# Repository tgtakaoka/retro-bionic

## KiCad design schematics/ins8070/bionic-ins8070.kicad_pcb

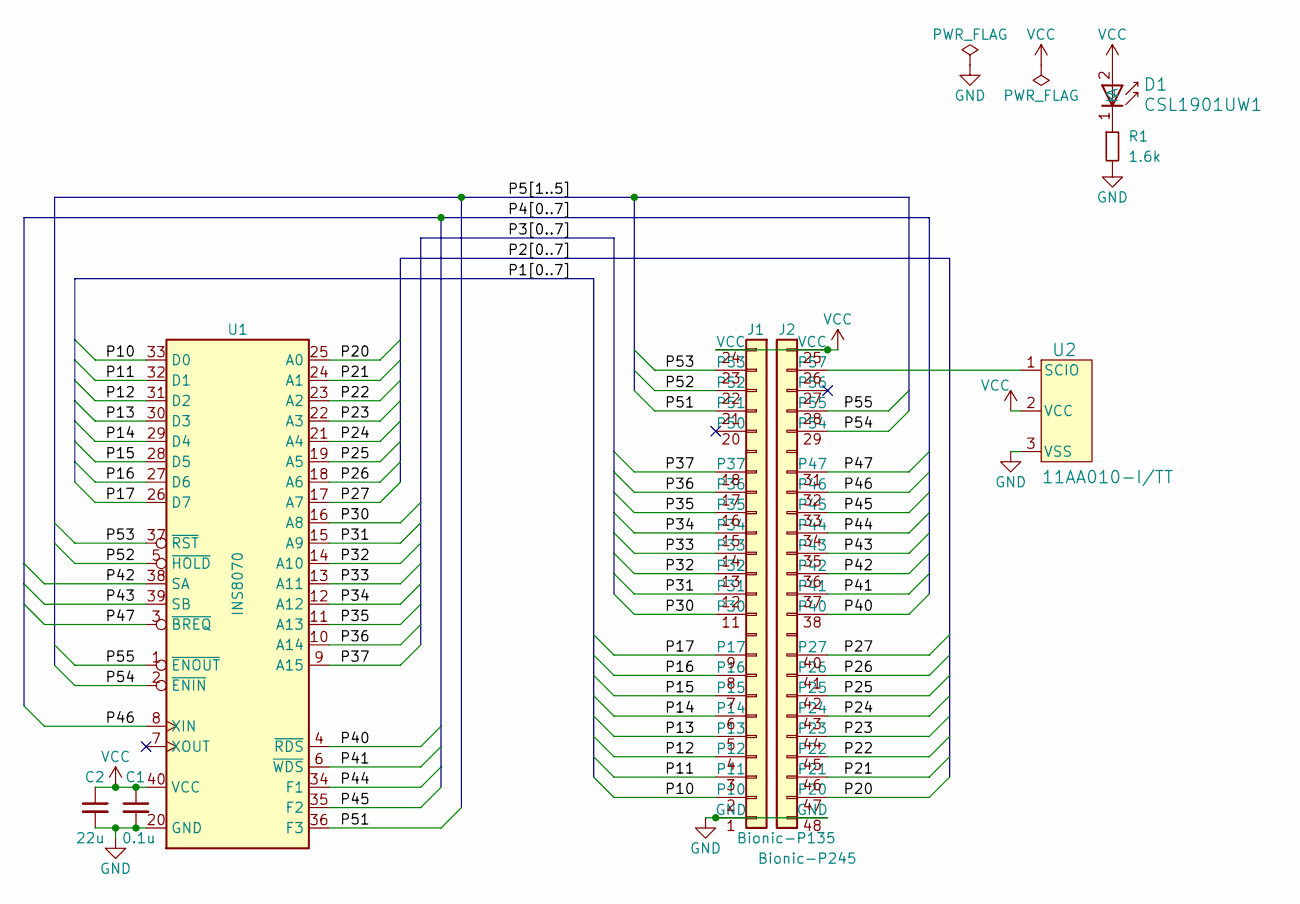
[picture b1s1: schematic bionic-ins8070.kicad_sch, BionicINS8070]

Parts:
C1: 0.1u; C_0603_1608Metric_Pad1.08x0.95mm_HandSolder
C2: 22u; C_0603_1608Metric_Pad1.08x0.95mm_HandSolder
D1: CSL1901UW1; LED_CSL1901UW1_ROM-M
J1: Bionic-P135; Bionic-P135_THT
J2: Bionic-P245; Bionic-P245_THT
R1: 1.6k; R_0603_1608Metric_Pad0.98x0.95mm_HandSolder
U1: INS8070; DIP-40_W15.24mm_Socket
U2: 11AA010-I/TT; SOT-23_MC_MCH-M

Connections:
/P10: J1.2 (P10), U1.33 (D0)
/P11: J1.3 (P11), U1.32 (D1)
/P12: J1.4 (P12), U1.31 (D2)
/P13: J1.5 (P13), U1.30 (D3)
/P14: J1.6 (P14), U1.29 (D4)
/P15: J1.7 (P15), U1.28 (D5)
/P16: J1.8 (P16), U1.27 (D6)
/P17: J1.9 (P17), U1.26 (D7)
/P20: J2.47 (P20), U1.25 (A0)
/P21: J2.46 (P21), U1.24 (A1)
/P22: J2.45 (P22), U1.23 (A2)
/P23: J2.44 (P23), U1.22 (A3)
/P24: J2.43 (P24), U1.21 (A4)
/P25: J2.42 (P25), U1.19 (A5)
/P26: J2.41 (P26), U1.18 (A6)
/P27: J2.40 (P27), U1.17 (A7)
/P30: J1.11 (P30), U1.16 (A8)
/P31: J1.12 (P31), U1.15 (A9)
/P32: J1.13 (P32), U1.14 (A10)
/P33: J1.14 (P33), U1.13 (A11)
/P34: J1.15 (P34), U1.12 (A12)
/P35: J1.16 (P35), U1.11 (A13)
/P36: J1.17 (P36), U1.10 (A14)
/P37: J1.18 (P37), U1.9 (A15)
/P40: J2.38 (P40), U1.4 (~RDS)
/P41: J2.37 (P41), U1.6 (~WDS)
/P42: J2.36 (P42), U1.38 (SA)
/P43: J2.35 (P43), U1.39 (SB)
/P44: J2.34 (P44), U1.34 (F1)
/P45: J2.33 (P45), U1.35 (F2)
/P46: J2.32 (P46), U1.8 (XIN)
/P47: J2.31 (P47), U1.3 (~BREQ)
/P51: J1.21 (P51), U1.36 (F3)
/P52: J1.22 (P52), U1.5 (~HOLD)
/P53: J1.23 (P53), U1.37 (~RST)
/P54: J2.29 (P54), U1.2 (~ENIN)
/P55: J2.28 (P55), U1.1 (~ENOUT)
GND: C1.2, C2.2, J1.1 (GND), J2.48 (GND), R1.2, U1.20 (GND), U2.3 (VSS)
unnamed: D1.1 (K), R1.1
unnamed: J2.26 (P57), U2.1 (SCIO)
VCC: C1.1, C2.1, D1.2 (A), J1.24 (VCC), J2.25 (VCC), U1.40 (VCC), U2.2 (VCC)

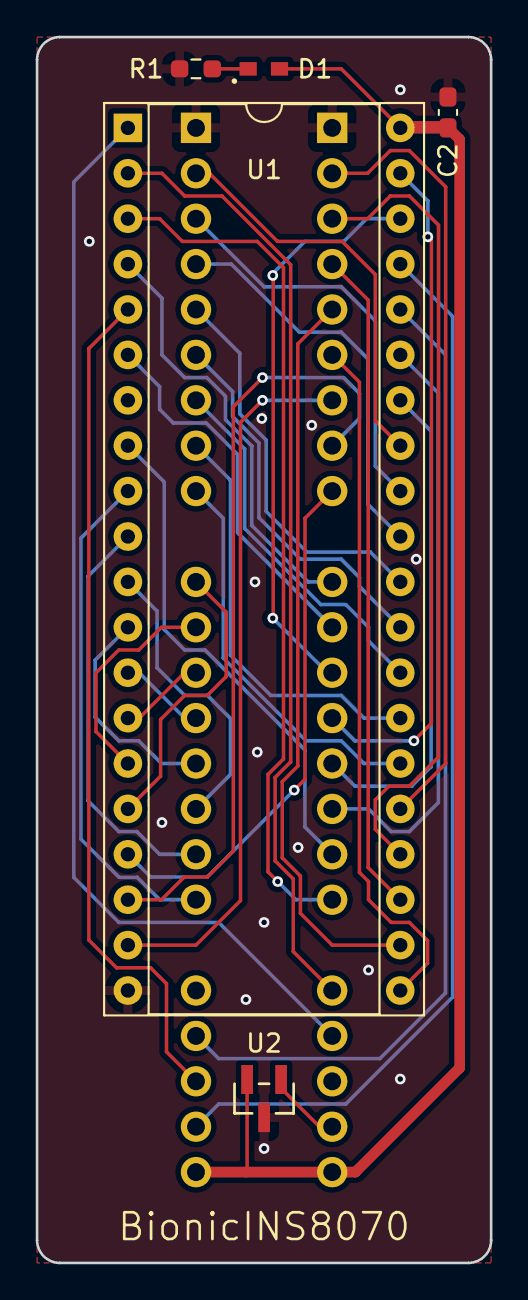
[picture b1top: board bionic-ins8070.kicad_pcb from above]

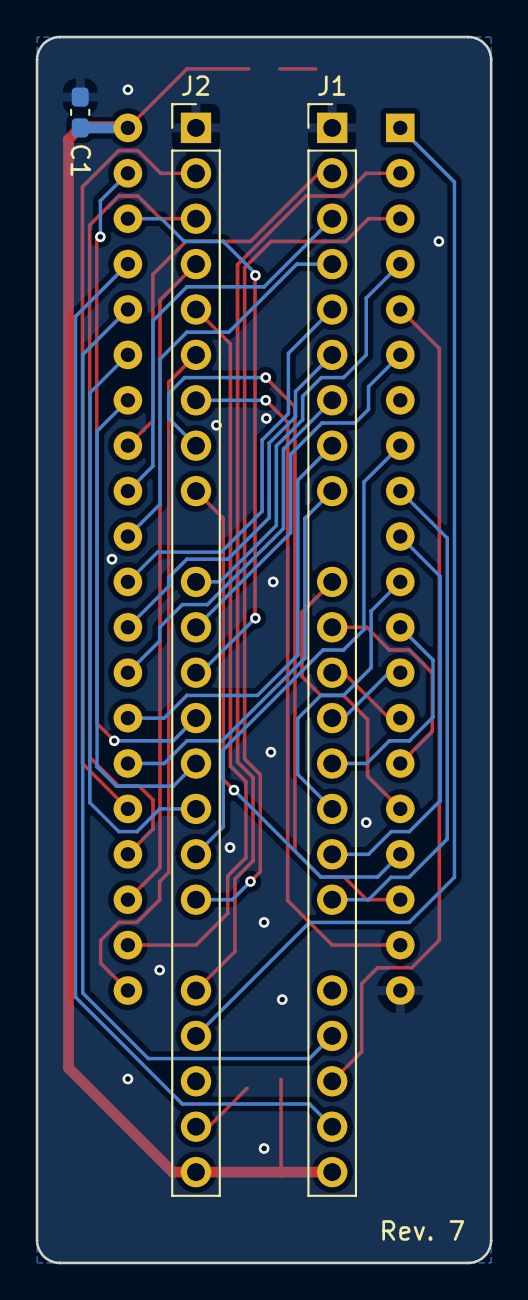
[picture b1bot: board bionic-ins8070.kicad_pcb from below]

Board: 2 copper layers, 25.4 x 68.6 mm, 8 parts (3 on the bottom side), 41 nets.

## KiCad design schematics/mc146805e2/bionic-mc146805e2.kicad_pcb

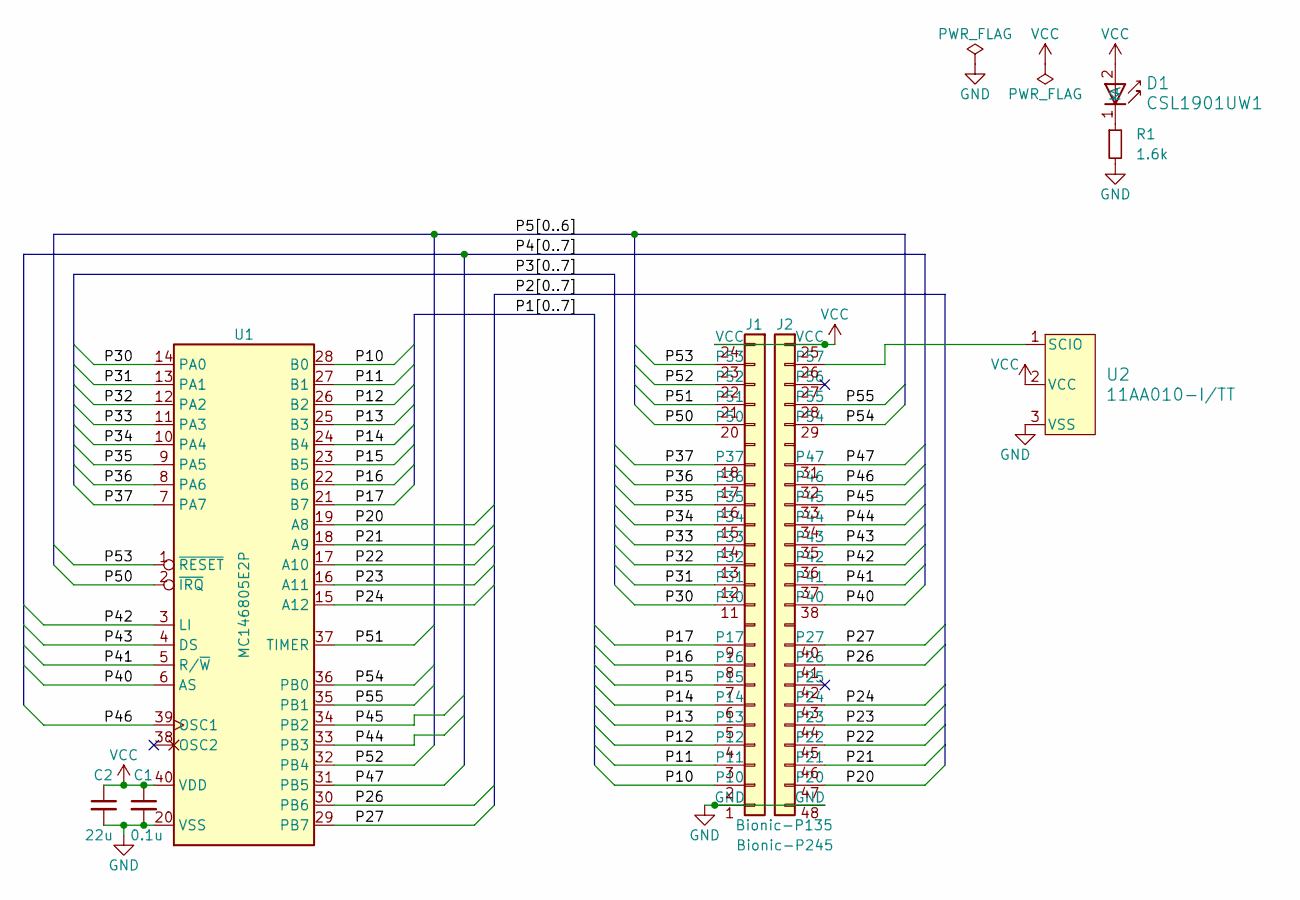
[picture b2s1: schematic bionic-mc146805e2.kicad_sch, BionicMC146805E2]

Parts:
C1: 0.1u; C_0603_1608Metric_Pad1.08x0.95mm_HandSolder
C2: 22u; C_0603_1608Metric_Pad1.08x0.95mm_HandSolder
D1: CSL1901UW1; LED_CSL1901UW1_ROM-M
J1: Bionic-P135; Bionic-P135_THT
J2: Bionic-P245; Bionic-P245_THT
R1: 1.6k; R_0603_1608Metric_Pad0.98x0.95mm_HandSolder
U1: MC146805E2P; DIP-40_W15.24mm_Socket
U2: 11AA010-I/TT; SOT-23_MC_MCH-M

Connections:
/P10: J1.2 (P10), U1.28 (B0)
/P11: J1.3 (P11), U1.27 (B1)
/P12: J1.4 (P12), U1.26 (B2)
/P13: J1.5 (P13), U1.25 (B3)
/P14: J1.6 (P14), U1.24 (B4)
/P15: J1.7 (P15), U1.23 (B5)
/P16: J1.8 (P16), U1.22 (B6)
/P17: J1.9 (P17), U1.21 (B7)
/P20: J2.47 (P20), U1.19 (A8)
/P21: J2.46 (P21), U1.18 (A9)
/P22: J2.45 (P22), U1.17 (A10)
/P23: J2.44 (P23), U1.16 (A11)
/P24: J2.43 (P24), U1.15 (A12)
/P26: J2.41 (P26), U1.30 (PB6)
/P27: J2.40 (P27), U1.29 (PB7)
/P30: J1.11 (P30), U1.14 (PA0)
/P31: J1.12 (P31), U1.13 (PA1)
/P32: J1.13 (P32), U1.12 (PA2)
/P33: J1.14 (P33), U1.11 (PA3)
/P34: J1.15 (P34), U1.10 (PA4)
/P35: J1.16 (P35), U1.9 (PA5)
/P36: J1.17 (P36), U1.8 (PA6)
/P37: J1.18 (P37), U1.7 (PA7)
/P40: J2.38 (P40), U1.6 (AS)
/P41: J2.37 (P41), U1.5 (R/~W)
/P42: J2.36 (P42), U1.3 (LI)
/P43: J2.35 (P43), U1.4 (DS)
/P44: J2.34 (P44), U1.33 (PB3)
/P45: J2.33 (P45), U1.34 (PB2)
/P46: J2.32 (P46), U1.39 (OSC1)
/P47: J2.31 (P47), U1.31 (PB5)
/P50: J1.20 (P50), U1.2 (~IRQ)
/P51: J1.21 (P51), U1.37 (TIMER)
/P52: J1.22 (P52), U1.32 (PB4)
/P53: J1.23 (P53), U1.1 (~RESET)
/P54: J2.29 (P54), U1.36 (PB0)
/P55: J2.28 (P55), U1.35 (PB1)
GND: C1.2, C2.2, J1.1 (GND), J2.48 (GND), R1.2, U1.20 (VSS), U2.3 (VSS)
unnamed: D1.1 (K), R1.1
unnamed: J2.26 (P57), U2.1 (SCIO)
VCC: C1.1, C2.1, D1.2 (A), J1.24 (VCC), J2.25 (VCC), U1.40 (VDD), U2.2 (VCC)

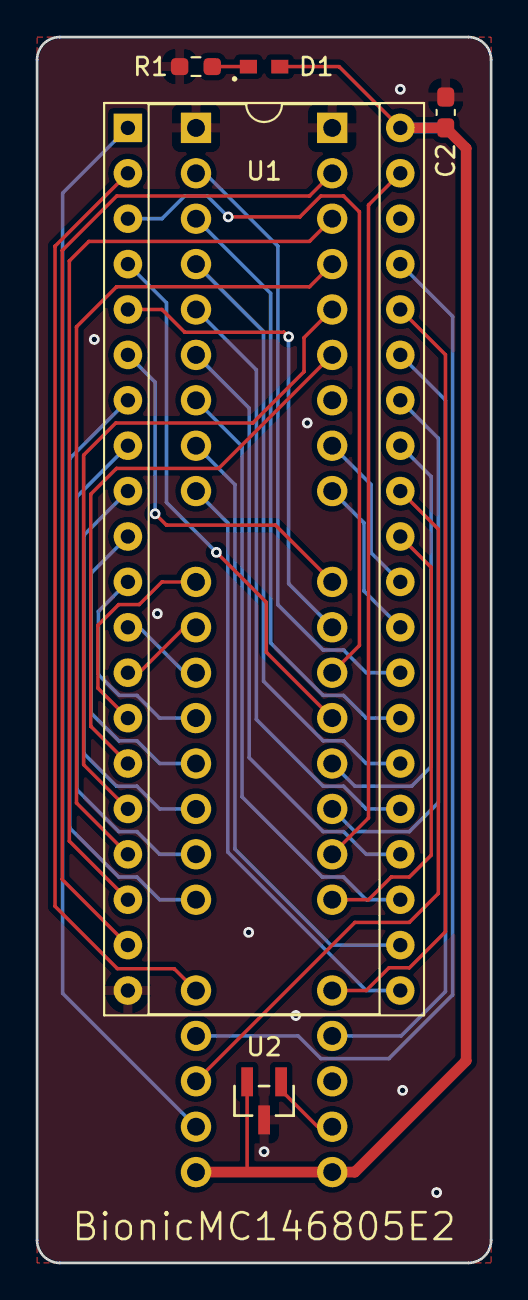
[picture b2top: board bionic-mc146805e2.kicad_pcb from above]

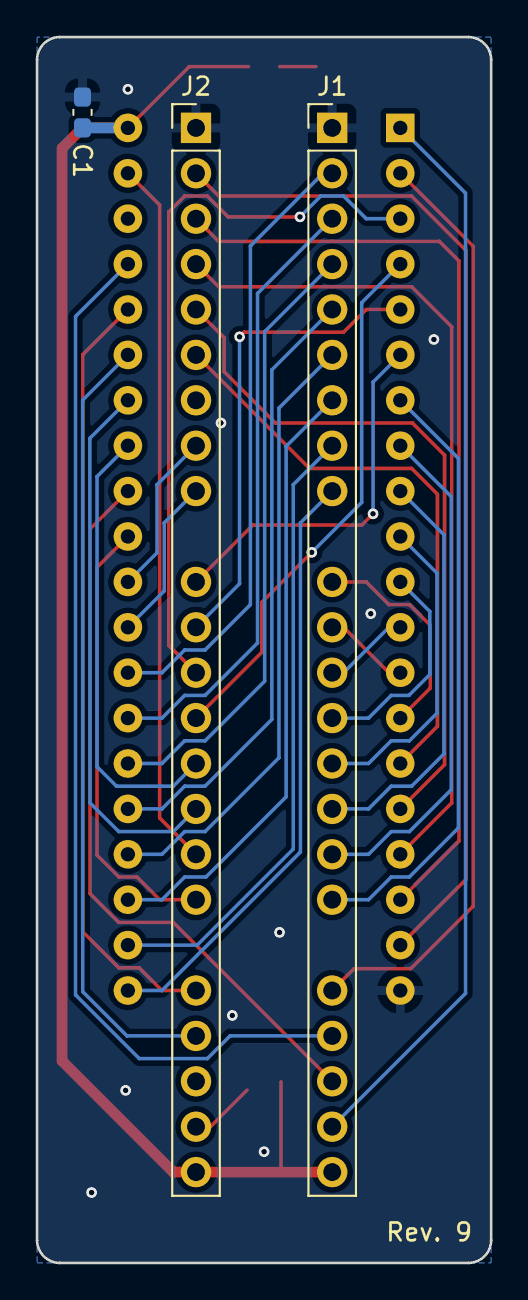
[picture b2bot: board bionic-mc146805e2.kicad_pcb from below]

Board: 2 copper layers, 25.4 x 68.6 mm, 8 parts (3 on the bottom side), 41 nets.

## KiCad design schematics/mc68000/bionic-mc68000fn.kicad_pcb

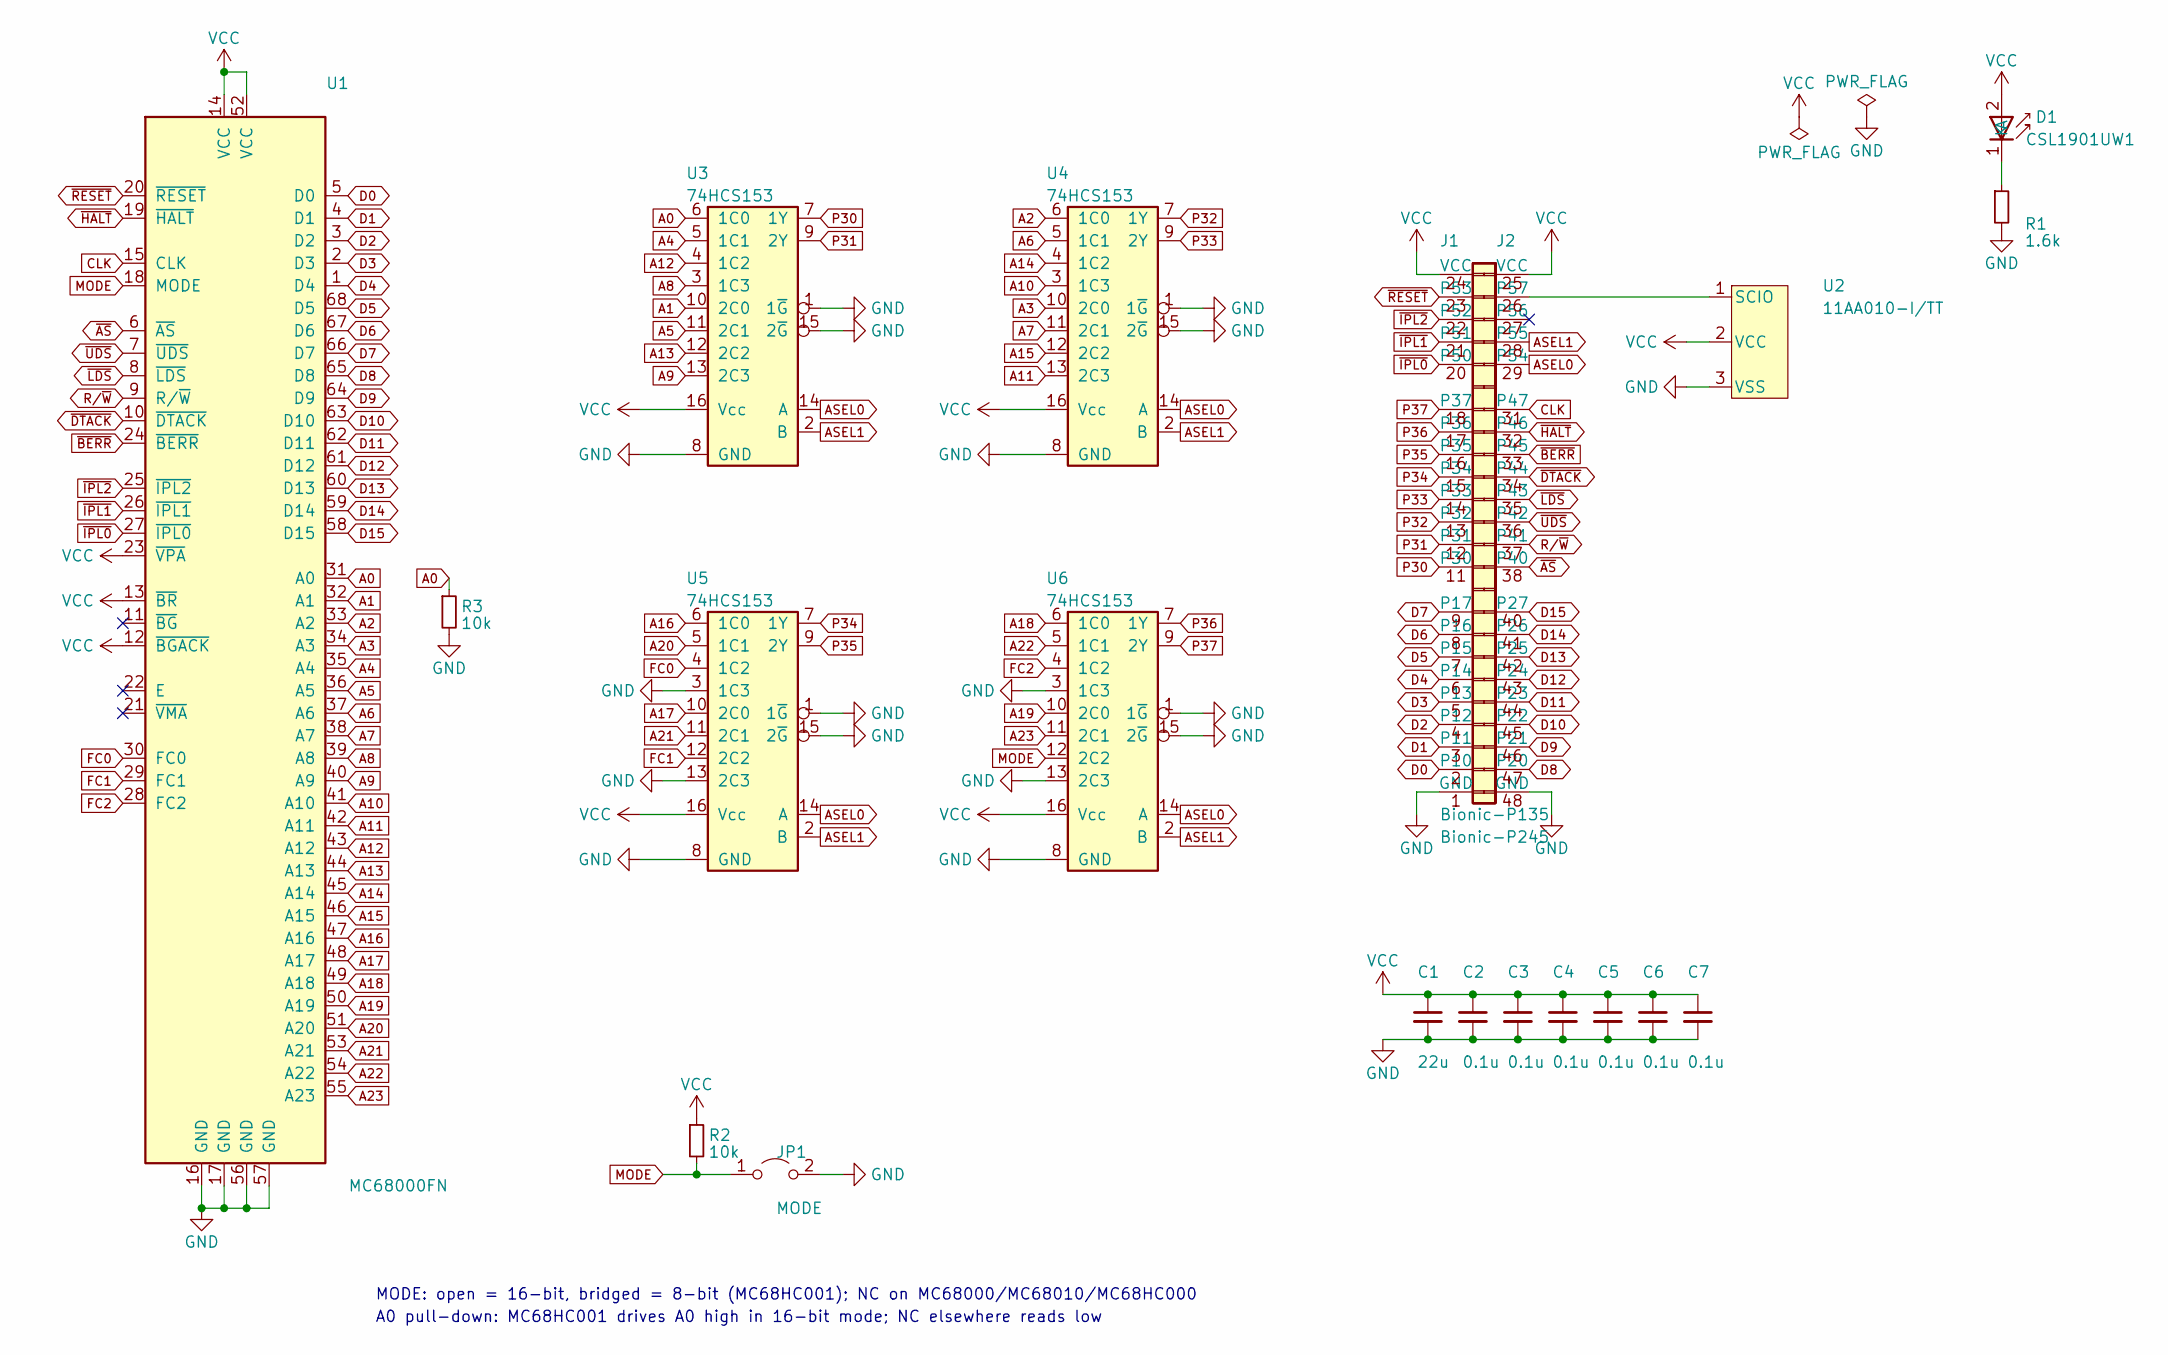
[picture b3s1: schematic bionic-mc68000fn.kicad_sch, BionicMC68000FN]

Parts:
C1: 22u; C_0603_1608Metric_Pad1.08x0.95mm_HandSolder
C2, C3, C4, C5, C6, C7: 0.1u; C_0603_1608Metric_Pad1.08x0.95mm_HandSolder
D1: CSL1901UW1; LED_CSL1901UW1_ROM-M
J1: Bionic-P135; Bionic-P135_SMT
J2: Bionic-P245; Bionic-P245_SMT
JP1: MODE; SolderJumper-2_P1.3mm_Open_RoundedPad1.0x1.5mm
R1: 1.6k; R_0603_1608Metric_Pad0.98x0.95mm_HandSolder
R2, R3: 10k; R_0603_1608Metric_Pad0.98x0.95mm_HandSolder
U1: MC68000FN; PLCC-68_SMD-Socket
U2: 11AA010-I/TT; SOT-23_MC_MCH-M
U3, U4, U5, U6: 74HCS153; PW16-M

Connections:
A0: R3.1, U1.31 (A0), U3.6 (1C0)
A1: U1.32 (A1), U3.10 (2C0)
A2: U1.33 (A2), U4.6 (1C0)
A3: U1.34 (A3), U4.10 (2C0)
A4: U1.35 (A4), U3.5 (1C1)
A5: U1.36 (A5), U3.11 (2C1)
A6: U1.37 (A6), U4.5 (1C1)
A7: U1.38 (A7), U4.11 (2C1)
A8: U1.39 (A8), U3.3 (1C3)
A9: U1.40 (A9), U3.13 (2C3)
A10: U1.41 (A10), U4.3 (1C3)
A11: U1.42 (A11), U4.13 (2C3)
A12: U1.43 (A12), U3.4 (1C2)
A13: U1.44 (A13), U3.12 (2C2)
A14: U1.45 (A14), U4.4 (1C2)
A15: U1.46 (A15), U4.12 (2C2)
A16: U1.47 (A16), U5.6 (1C0)
A17: U1.48 (A17), U5.10 (2C0)
A18: U1.49 (A18), U6.6 (1C0)
A19: U1.50 (A19), U6.10 (2C0)
A20: U1.51 (A20), U5.5 (1C1)
A21: U1.53 (A21), U5.11 (2C1)
A22: U1.54 (A22), U6.5 (1C1)
A23: U1.55 (A23), U6.11 (2C1)
ASEL0: J2.29 (P54), U3.14 (A), U4.14 (A), U5.14 (A), U6.14 (A)
ASEL1: J2.28 (P55), U3.2 (B), U4.2 (B), U5.2 (B), U6.2 (B)
CLK: J2.31 (P47), U1.15 (CLK)
D0: J1.2 (P10), U1.5 (D0)
D1: J1.3 (P11), U1.4 (D1)
D2: J1.4 (P12), U1.3 (D2)
D3: J1.5 (P13), U1.2 (D3)
D4: J1.6 (P14), U1.1 (D4)
D5: J1.7 (P15), U1.68 (D5)
D6: J1.8 (P16), U1.67 (D6)
D7: J1.9 (P17), U1.66 (D7)
D8: J2.47 (P20), U1.65 (D8)
D9: J2.46 (P21), U1.64 (D9)
D10: J2.45 (P22), U1.63 (D10)
D11: J2.44 (P23), U1.62 (D11)
D12: J2.43 (P24), U1.61 (D12)
D13: J2.42 (P25), U1.60 (D13)
D14: J2.41 (P26), U1.59 (D14)
D15: J2.40 (P27), U1.58 (D15)
FC0: U1.30 (FC0), U5.4 (1C2)
FC1: U1.29 (FC1), U5.12 (2C2)
FC2: U1.28 (FC2), U6.4 (1C2)
GND: C1.2, C2.2, C3.2, C4.2, C5.2, C6.2, C7.2, J1.1 (GND), J2.48 (GND), JP1.2 (B), R1.2, R3.2, U1.16 (GND), U1.17 (GND), U1.56 (GND), U1.57 (GND), U2.3 (VSS), U3.1 (1~G), U3.8 (GND), U3.15 (2~G), U4.1 (1~G), U4.8 (GND), U4.15 (2~G), U5.1 (1~G), U5.3 (1C3), U5.8 (GND), U5.13 (2C3), U5.15 (2~G), U6.1 (1~G), U6.3 (1C3), U6.8 (GND), U6.13 (2C3), U6.15 (2~G)
MODE: JP1.1 (A), R2.2, U1.18 (MODE), U6.12 (2C2)
unnamed: D1.1 (K), R1.1
unnamed: J2.26 (P57), U2.1 (SCIO)
P30: J1.11 (P30), U3.7 (1Y)
P31: J1.12 (P31), U3.9 (2Y)
P32: J1.13 (P32), U4.7 (1Y)
P33: J1.14 (P33), U4.9 (2Y)
P34: J1.15 (P34), U5.7 (1Y)
P35: J1.16 (P35), U5.9 (2Y)
P36: J1.17 (P36), U6.7 (1Y)
P37: J1.18 (P37), U6.9 (2Y)
R/~W: J2.37 (P41), U1.9 (R/~W)
VCC: C1.1, C2.1, C3.1, C4.1, C5.1, C6.1, C7.1, D1.2 (A), J1.24 (VCC), J2.25 (VCC), R2.1, U1.12 (~BGACK), U1.13 (~BR), U1.14 (VCC), U1.23 (~VPA), U1.52 (VCC), U2.2 (VCC), U3.16 (Vcc), U4.16 (Vcc), U5.16 (Vcc), U6.16 (Vcc)
~AS: J2.38 (P40), U1.6 (~AS)
~BERR: J2.33 (P45), U1.24 (~BERR)
~DTACK: J2.34 (P44), U1.10 (~DTACK)
~HALT: J2.32 (P46), U1.19 (~HALT)
~IPL0: J1.20 (P50), U1.27 (~IPL0)
~IPL1: J1.21 (P51), U1.26 (~IPL1)
~IPL2: J1.22 (P52), U1.25 (~IPL2)
~LDS: J2.35 (P43), U1.8 (~LDS)
~RESET: J1.23 (P53), U1.20 (~RESET)
~UDS: J2.36 (P42), U1.7 (~UDS)

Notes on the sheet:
MODE: open = 16-bit, bridged = 8-bit (MC68HC001); NC on MC68000/MC68010/MC68HC000
A0 pull-down: MC68HC001 drives A0 high in 16-bit mode; NC elsewhere reads low

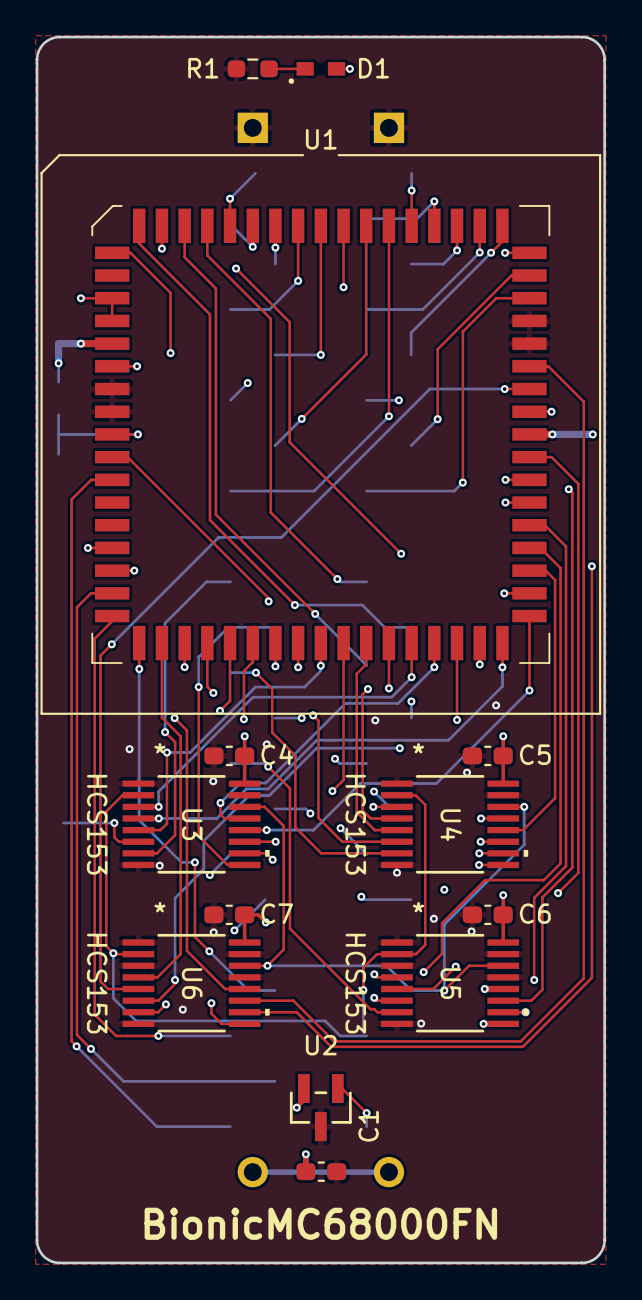
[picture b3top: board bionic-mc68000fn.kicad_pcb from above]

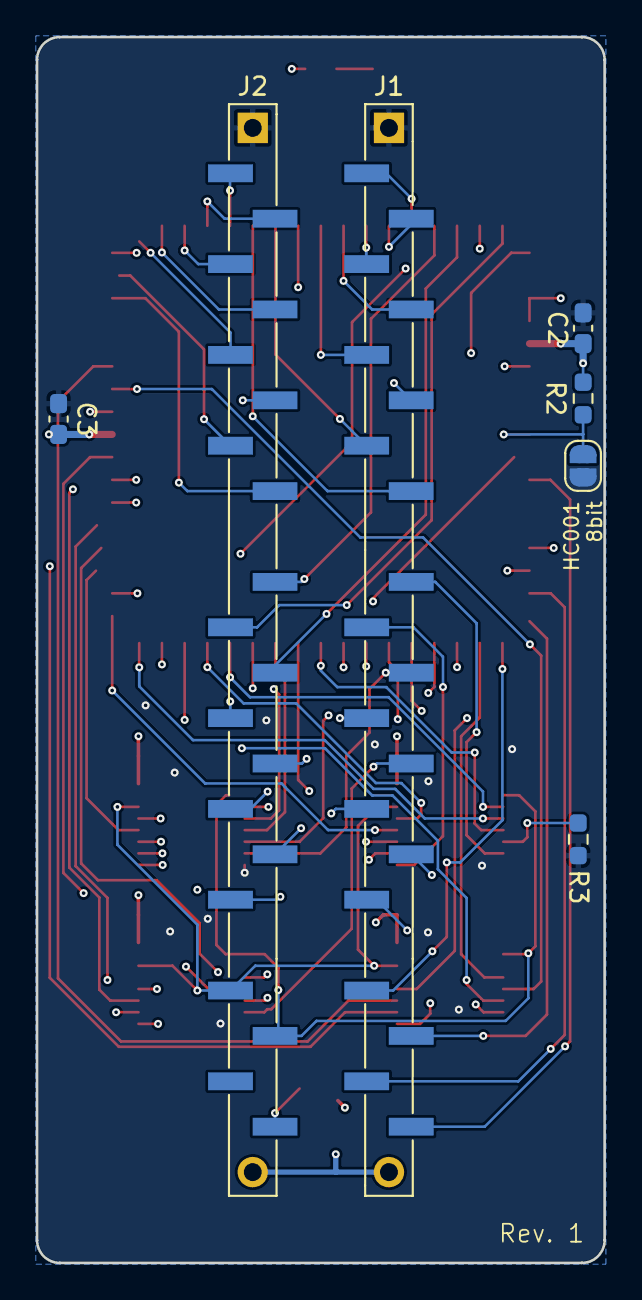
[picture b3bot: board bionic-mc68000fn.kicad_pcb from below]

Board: 4 copper layers, 31.7 x 68.6 mm, 20 parts (7 on the bottom side), 70 nets.

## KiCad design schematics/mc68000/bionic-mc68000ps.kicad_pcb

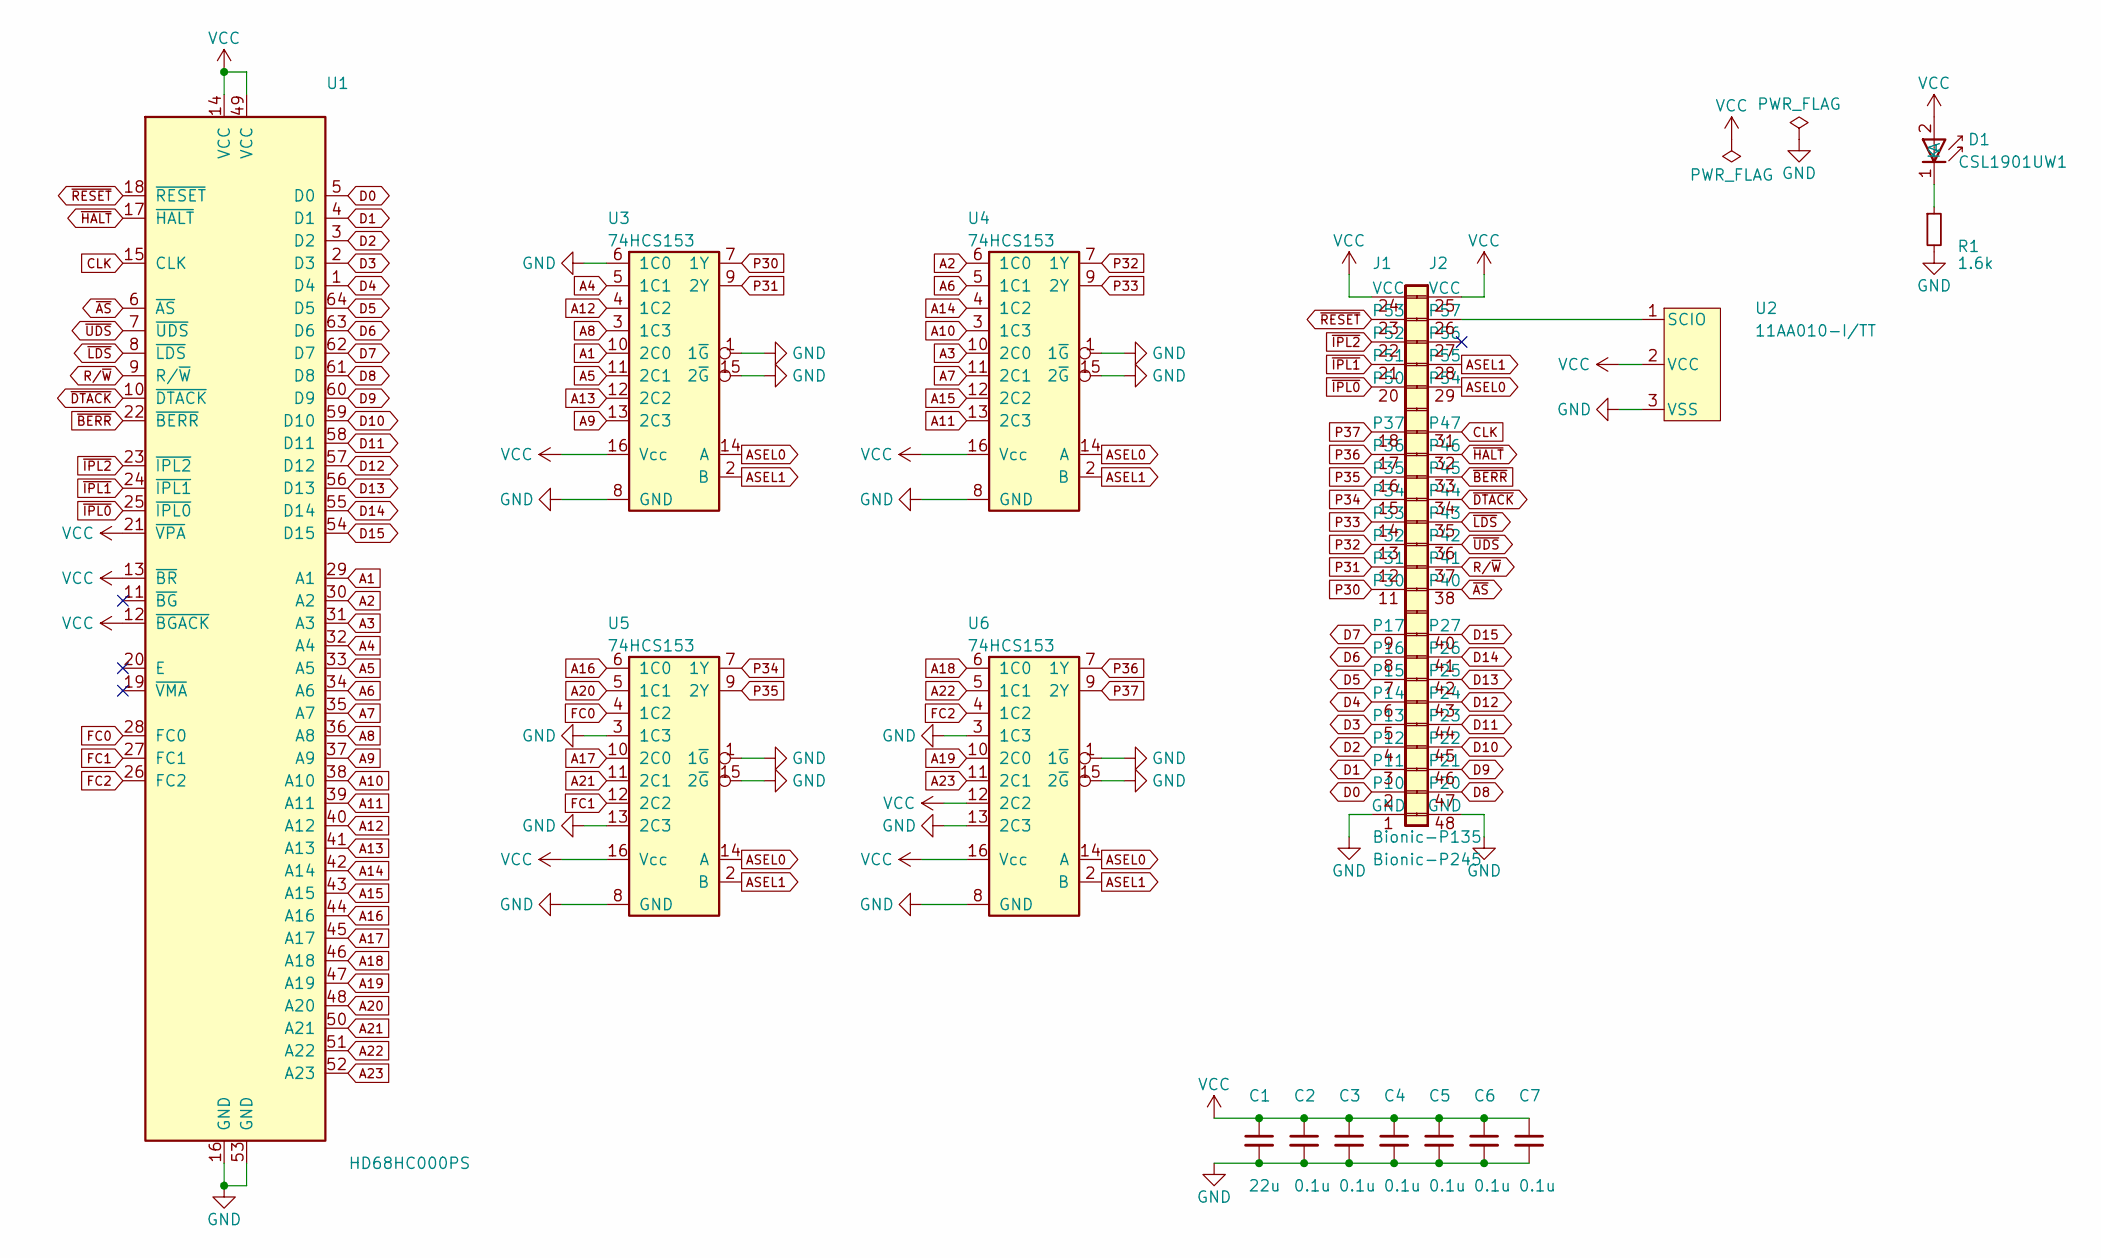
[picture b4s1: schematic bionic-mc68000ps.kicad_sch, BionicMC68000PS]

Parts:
C1: 22u; C_0603_1608Metric_Pad1.08x0.95mm_HandSolder
C2, C3, C4, C5, C6, C7: 0.1u; C_0603_1608Metric_Pad1.08x0.95mm_HandSolder
D1: CSL1901UW1; LED_CSL1901UW1_ROM-M
J1: Bionic-P135; Bionic-P135_SMT
J2: Bionic-P245; Bionic-P245_SMT
R1: 1.6k; R_0603_1608Metric_Pad0.98x0.95mm_HandSolder
U1: HD68HC000PS; SDIP-64_W19.05mm_Socket
U2: 11AA010-I/TT; SOT-23_MC_MCH-M
U3, U4, U5, U6: 74HCS153; PW16-M

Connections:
A1: U1.29 (A1), U3.10 (2C0)
A2: U1.30 (A2), U4.6 (1C0)
A3: U1.31 (A3), U4.10 (2C0)
A4: U1.32 (A4), U3.5 (1C1)
A5: U1.33 (A5), U3.11 (2C1)
A6: U1.34 (A6), U4.5 (1C1)
A7: U1.35 (A7), U4.11 (2C1)
A8: U1.36 (A8), U3.3 (1C3)
A9: U1.37 (A9), U3.13 (2C3)
A10: U1.38 (A10), U4.3 (1C3)
A11: U1.39 (A11), U4.13 (2C3)
A12: U1.40 (A12), U3.4 (1C2)
A13: U1.41 (A13), U3.12 (2C2)
A14: U1.42 (A14), U4.4 (1C2)
A15: U1.43 (A15), U4.12 (2C2)
A16: U1.44 (A16), U5.6 (1C0)
A17: U1.45 (A17), U5.10 (2C0)
A18: U1.46 (A18), U6.6 (1C0)
A19: U1.47 (A19), U6.10 (2C0)
A20: U1.48 (A20), U5.5 (1C1)
A21: U1.50 (A21), U5.11 (2C1)
A22: U1.51 (A22), U6.5 (1C1)
A23: U1.52 (A23), U6.11 (2C1)
ASEL0: J2.29 (P54), U3.14 (A), U4.14 (A), U5.14 (A), U6.14 (A)
ASEL1: J2.28 (P55), U3.2 (B), U4.2 (B), U5.2 (B), U6.2 (B)
CLK: J2.31 (P47), U1.15 (CLK)
D0: J1.2 (P10), U1.5 (D0)
D1: J1.3 (P11), U1.4 (D1)
D2: J1.4 (P12), U1.3 (D2)
D3: J1.5 (P13), U1.2 (D3)
D4: J1.6 (P14), U1.1 (D4)
D5: J1.7 (P15), U1.64 (D5)
D6: J1.8 (P16), U1.63 (D6)
D7: J1.9 (P17), U1.62 (D7)
D8: J2.47 (P20), U1.61 (D8)
D9: J2.46 (P21), U1.60 (D9)
D10: J2.45 (P22), U1.59 (D10)
D11: J2.44 (P23), U1.58 (D11)
D12: J2.43 (P24), U1.57 (D12)
D13: J2.42 (P25), U1.56 (D13)
D14: J2.41 (P26), U1.55 (D14)
D15: J2.40 (P27), U1.54 (D15)
FC0: U1.28 (FC0), U5.4 (1C2)
FC1: U1.27 (FC1), U5.12 (2C2)
FC2: U1.26 (FC2), U6.4 (1C2)
GND: C1.2, C2.2, C3.2, C4.2, C5.2, C6.2, C7.2, J1.1 (GND), J2.48 (GND), R1.2, U1.16 (GND), U1.53 (GND), U2.3 (VSS), U3.1 (1~G), U3.6 (1C0), U3.8 (GND), U3.15 (2~G), U4.1 (1~G), U4.8 (GND), U4.15 (2~G), U5.1 (1~G), U5.3 (1C3), U5.8 (GND), U5.13 (2C3), U5.15 (2~G), U6.1 (1~G), U6.3 (1C3), U6.8 (GND), U6.13 (2C3), U6.15 (2~G)
unnamed: D1.1 (K), R1.1
unnamed: J2.26 (P57), U2.1 (SCIO)
P30: J1.11 (P30), U3.7 (1Y)
P31: J1.12 (P31), U3.9 (2Y)
P32: J1.13 (P32), U4.7 (1Y)
P33: J1.14 (P33), U4.9 (2Y)
P34: J1.15 (P34), U5.7 (1Y)
P35: J1.16 (P35), U5.9 (2Y)
P36: J1.17 (P36), U6.7 (1Y)
P37: J1.18 (P37), U6.9 (2Y)
R/~W: J2.37 (P41), U1.9 (R/~W)
VCC: C1.1, C2.1, C3.1, C4.1, C5.1, C6.1, C7.1, D1.2 (A), J1.24 (VCC), J2.25 (VCC), U1.12 (~BGACK), U1.13 (~BR), U1.14 (VCC), U1.21 (~VPA), U1.49 (VCC), U2.2 (VCC), U3.16 (Vcc), U4.16 (Vcc), U5.16 (Vcc), U6.12 (2C2), U6.16 (Vcc)
~AS: J2.38 (P40), U1.6 (~AS)
~BERR: J2.33 (P45), U1.22 (~BERR)
~DTACK: J2.34 (P44), U1.10 (~DTACK)
~HALT: J2.32 (P46), U1.17 (~HALT)
~IPL0: J1.20 (P50), U1.25 (~IPL0)
~IPL1: J1.21 (P51), U1.24 (~IPL1)
~IPL2: J1.22 (P52), U1.23 (~IPL2)
~LDS: J2.35 (P43), U1.8 (~LDS)
~RESET: J1.23 (P53), U1.18 (~RESET)
~UDS: J2.36 (P42), U1.7 (~UDS)

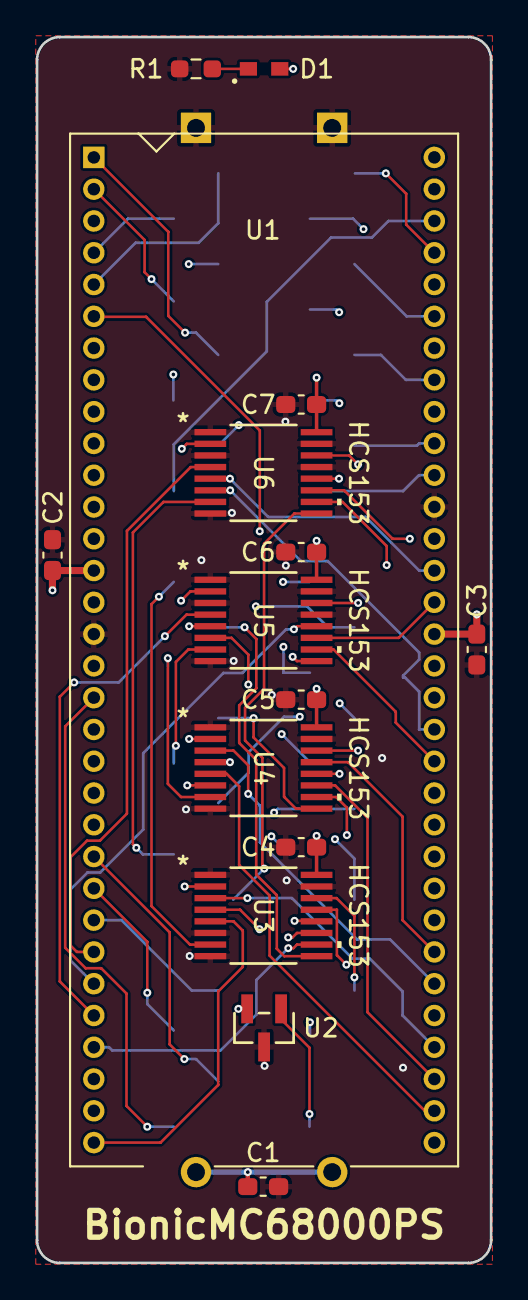
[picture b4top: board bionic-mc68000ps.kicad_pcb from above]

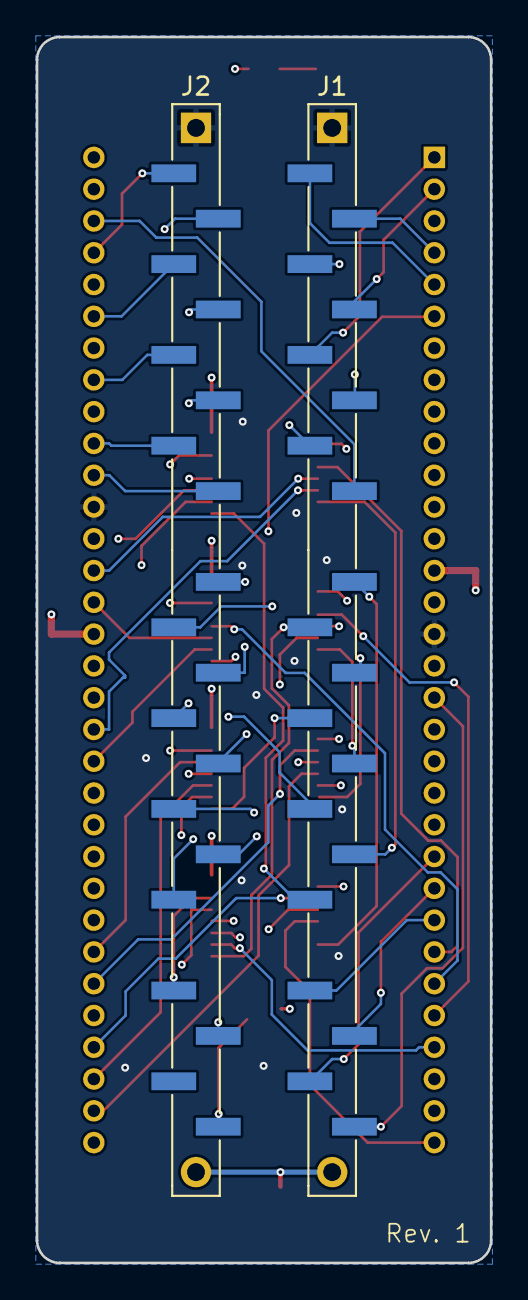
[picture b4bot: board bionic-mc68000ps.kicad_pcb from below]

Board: 4 copper layers, 25.4 x 68.6 mm, 17 parts (2 on the bottom side), 68 nets.

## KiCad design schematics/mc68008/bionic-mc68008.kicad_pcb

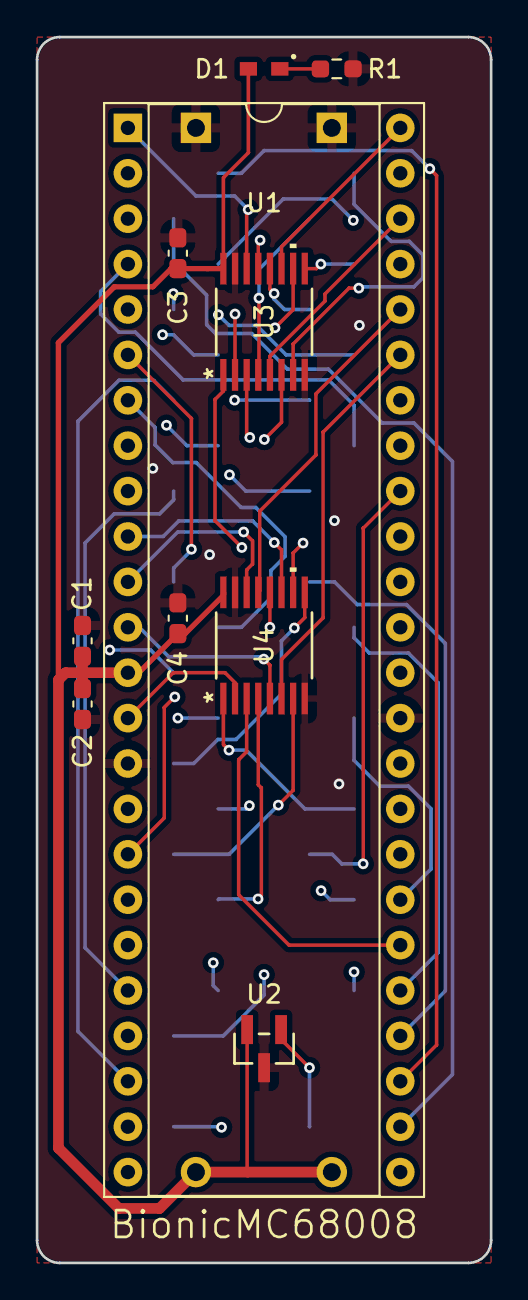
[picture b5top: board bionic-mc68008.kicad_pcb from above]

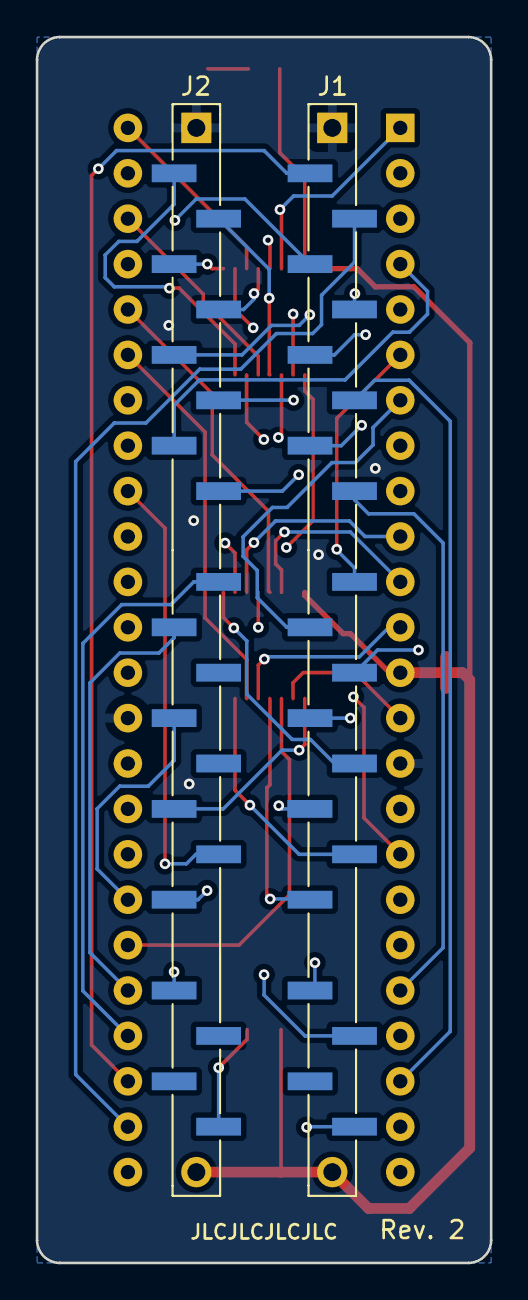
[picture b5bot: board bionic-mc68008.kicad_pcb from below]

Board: 4 copper layers, 25.4 x 68.6 mm, 12 parts (2 on the bottom side), 54 nets.

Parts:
C1, C3, C4: 0.1u; C_0603_1608Metric_Pad1.08x0.95mm_HandSolder
C2: 22u; C_0603_1608Metric_Pad1.08x0.95mm_HandSolder
D1: CSL1901UW1; LED_CSL1901UW1_ROM-M
J1: Bionic-P135; Bionic-P135_SMT
J2: Bionic-P245; Bionic-P245_SMT
R1: 1.6k; R_0603_1608Metric_Pad0.98x0.95mm_HandSolder
U1: MC68008P; DIP-48_W15.24mm_Socket
U2: 11AA010-I/TT; SOT-23_MC_MCH-M
U3, U4: 74AHCT157; PW16-M

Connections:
/A0: U1.46 (A0), U3.5 (2I0)
/A1: U1.47 (A1), U3.2 (1I0)
/A2: U1.48 (A2), U3.11 (3I0)
/A3: U1.1 (A3), U3.14 (4I0)
/A12: U1.10 (A12), U4.11 (3I0)
/A13: U1.11 (A13), U4.14 (4I0)
/A14: U1.12 (A14), U4.5 (2I0)
/A15: U1.14 (A15), U4.2 (1I0)
/A16: U1.16 (A16), U3.6 (2I1)
/A17: U1.17 (A17), U3.3 (1I1)
/A18: U1.18 (A18), U3.10 (3I1)
/A19: U1.19 (A19), U3.13 (4I1)
/FC0: U1.45 (FC0), U4.10 (3I1)
/FC1: U1.44 (FC1), U4.13 (4I1)
/FC2: U1.43 (FC2), U4.6 (2I1)
/FC3: U1.30 (R/~W), U4.3 (1I1)
/P10: J1.2 (P10), U1.27 (D0)
/P11: J1.3 (P11), U1.26 (D1)
/P12: J1.4 (P12), U1.25 (D2)
/P13: J1.5 (P13), U1.24 (D3)
/P14: J1.6 (P14), U1.23 (D4)
/P15: J1.7 (P15), U1.22 (D5)
/P16: J1.8 (P16), U1.21 (D6)
/P17: J1.9 (P17), U1.20 (D7)
/P20: J2.47 (P20), U3.7 (2Y)
/P21: J2.46 (P21), U3.4 (1Y)
/P22: J2.45 (P22), U3.9 (3Y)
/P23: J2.44 (P23), U3.12 (4Y)
/P24: J2.43 (P24), U1.2 (A4)
/P25: J2.42 (P25), U1.3 (A5)
/P26: J2.41 (P26), U1.4 (A6)
/P27: J2.40 (P27), U1.5 (A7)
/P30: J1.11 (P30), U1.6 (A8)
/P31: J1.12 (P31), U1.7 (A9)
/P32: J1.13 (P32), U1.8 (A10)
/P33: J1.14 (P33), U1.9 (A11)
/P34: J1.15 (P34), U4.9 (3Y)
/P35: J1.16 (P35), U4.12 (4Y)
/P36: J1.17 (P36), U4.7 (2Y)
/P37: J1.18 (P37), U4.4 (1Y)
/P40: J2.38 (P40), U1.28 (~AS)
/P41: J2.37 (P41), U1.29 (~DS)
/P43: J2.35 (P43), U1.31 (~DTACK)
/P45: J2.33 (P45), U3.1 (S), U4.1 (S)
/P46: J2.32 (P46), U1.40 (~BERR)
/P47: J2.31 (P47), U1.34 (CLK)
/P50: J1.20 (P50), U1.42 (~IPL20)
/P51: J1.21 (P51), U1.41 (~IPL1)
/P53: J1.23 (P53), U1.37 (~RESET)
/P54: J2.29 (P54), U1.36 (~HALT)
GND: C1.2, C2.2, C3.2, C4.2, J1.1 (GND), J2.48 (GND), R1.2, U1.15 (GND), U1.35 (GND), U2.3 (VSS), U3.8 (GND), U3.15 (~E), U4.8 (GND), U4.15 (~E)
unnamed: D1.1 (K), R1.1
unnamed: J2.26 (P57), U2.1 (SCIO)
VCC: C1.1, C2.1, C3.1, C4.1, D1.2 (A), J1.24 (VCC), J2.25 (VCC), U1.13 (VCC), U1.33 (~BR), U2.2 (VCC), U3.16 (Vcc), U4.16 (Vcc)
